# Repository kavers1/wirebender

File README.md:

# Wirebender

This project will build a wire bender

3D designs are shared in STL format. 
The 3D model is available as a Fusion 360 project [Wire bender](https://myhub.autodesk360.com/ue2954c30/g/projects/20200113254731651/data/dXJuOmFkc2sud2lwcHJvZDpmcy5mb2xkZXI6Y28uQzlzSklFZG9SLW1GWHdSQ3duYzF3QQ)

inspiration can be found in 
  - [LiveWire](https://www.thingiverse.com/thing:1786839)
  - [Precise Wire Bending Machine](https://hackaday.io/project/166369-precise-wire-bending-machine)
  - [DIY-wire-bender](https://hackaday.com/2018/10/14/diy-wire-bender-gets-wires-all-bent-into-shape/)

The aim of the project is to combine best of both world and come up with a precise 3D wire bender.

## ESP32-Grbl Controller

This part of the project is based on the project or bdring's [Grbl_ESP32_MPCNC_Controller](https://github.com/bdring/Grbl_ESP32_MPCNC_Controller/) with addition of 2 servo axis, which will be used in our wire bending project.
This ReadMe file is mostly a copy of the original project. As we go we will adapt the content.

This is a CNC controller specially designed to address the needs of the [MPCNC (Mostly Printed CNC) CNC Router](https://www.v1engineering.com/specifications/).
Secondary X and Y axises can be used as servo outputs. This will be usefull for the wirebender project.

### Features

- ESP32 Microcontroller:
  - Very Fast: Dual core 32 bit, 240 MHz
  - Large Flash Memory
  - Wifi:
  - Bluetooth:
- Grbl_ESP32 Firmware:
  - Compatible with most existing Grbl gcode sender software.
  - Web User Interface
  - Multiple Interfaces
    - USB Serial:
    - Web User Interface:
    - Telnet:
    - Bluetooth:
    - SD Card:
- (5) Stepper Motor Drivers: On for each motor in the MPCNC design. Motors are ganging in firmware and have an auto squaring feature executed during homing.
- Limit Switch Connectors: 
- Control Pins:
- Spindle Control:
- Fan Power: 
- Micro SD card: 
- X,Y,Z axis with double motor drivers for X and Y axis drive. These double axis can be disabled and converted to servo axis.

### Credits

To our inspiration [Grbl_ESP32](https://github.com/bdring/Grbl_Esp32)

### Usage Instructions
see original project
[See the wiki](https://github.com/bdring/Grbl_ESP32_MPCNC_Controller/wiki)

### License

Creative Commons Attribution - ShareAlike 4.0 International

There are no commercial restrictions on using this design, but you must attribute the design to Bart Dring or @buildlog. You must also publish any changes or improvements to the design with the same open source license.  

This project is a modification of Bart Drings 

### Version History

- Version 1.0 Original upload ported to Kicad. Added LED support on limits.

### Source Files

- [Firmware](https://github.com/bdring/Grbl_Esp32) to be updated to support servos.
- [Kicad Source](https://github.com/kavers1/wirebender/tree/master/Hardware/ESP32-cnc)
- [Gerber Files](https://github.com/kavers1/wirebender/tree/master/Hardware/ESP32-cnc/gerber)
- [Schematic](https://github.com/kavers1/wirebender/blob/master/Hardware/ESP32-cnc/ESP32-cnc.pdf)
- [imported Kicad Models](https://github.com/kavers1/wirebender/tree/master/Hardware/Kicad_Libs)

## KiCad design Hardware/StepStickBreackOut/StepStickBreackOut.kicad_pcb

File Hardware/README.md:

# Wirebender

## ESP32-Grbl Controller

This project is based on the project or bdring's [Grbl_ESP32_MPCNC_Controller](https://github.com/bdring/Grbl_ESP32_MPCNC_Controller/) with addition of 2 servo axis, which will be used in our wire bending project.
This ReadMe file is mostly a copy of the original project. As we go we will adapt the content.

This is a CNC controller specially designed to address the needs of the [MPCNC (Mostly Printed CNC) CNC Router](https://www.v1engineering.com/specifications/).
Secondary X and Y axises can be used as servo outputs. This will be usefull for the wirebender project.

### Features

- ESP32 Microcontroller:
  - Very Fast: Dual core 32 bit, 240 MHz
  - Large Flash Memory
  - Wifi:
  - Bluetooth:
- Grbl_ESP32 Firmware:
  - Compatible with most existing Grbl gcode sender software.
  - Web User Interface
  - Multiple Interfaces
    - USB Serial:
    - Web User Interface:
    - Telnet:
    - Bluetooth:
    - SD Card:
- (5) Stepper Motor Drivers: On for each motor in the MPCNC design. Motors are ganging in firmware and have an auto squaring feature executed during homing.
- Limit Switch Connectors: 
- Control Pins:
- Spindle Control:
- Fan Power: 
- Micro SD card: 
- X,Y,Z axis with double motor drivers for X and Y axis drive. These double axis can be disabled and converted to servo axis.

### Credits

To our inspiration [Grbl_ESP32](https://github.com/bdring/Grbl_Esp32)

### Usage Instructions
see original project
[See the wiki](https://github.com/bdring/Grbl_ESP32_MPCNC_Controller/wiki)

### License

Creative Commons Attribution - ShareAlike 4.0 International

There are no commercial restrictions on using this design, but you must attribute the design to Bart Dring or @buildlog. You must also publish any changes or improvements to the design with the same open source license.  

This project is a modification of Bart Drings 

### Version History

- Version 1.0 Original upload ported to Kicad. Added LED support on limits.

### Source Files

- [Firmware](https://github.com/bdring/Grbl_Esp32) to be updated to support servos.
- [Kicad Source](https://github.com/kavers1/wirebender/tree/master/Hardware/ESP32-cnc)
- [Gerber Files](https://github.com/kavers1/wirebender/tree/master/Hardware/ESP32-cnc/gerber)
- [Schematic](https://github.com/kavers1/wirebender/blob/master/Hardware/ESP32-cnc/ESP32-cnc.pdf)
- [imported Kicad Models](https://github.com/kavers1/wirebender/tree/master/Hardware/Kicad_Libs)

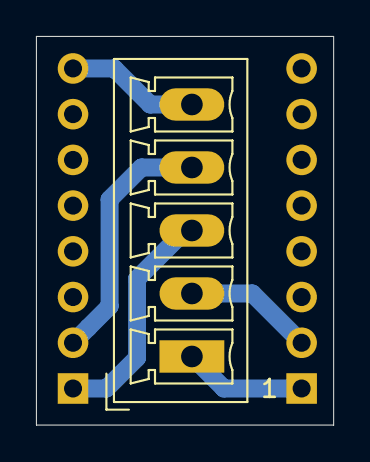
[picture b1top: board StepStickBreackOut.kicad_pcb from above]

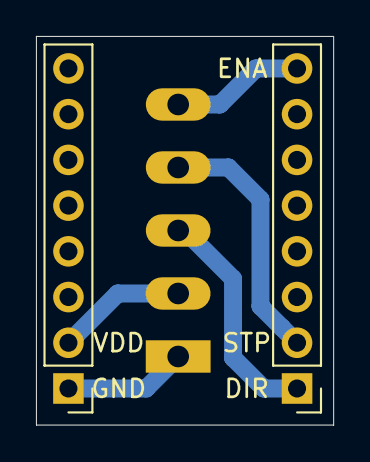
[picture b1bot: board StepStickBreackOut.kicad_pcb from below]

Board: 2 copper layers, 16.5 x 21.6 mm, 3 parts (2 on the bottom side), 5 nets.

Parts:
J1, J3: Conn_01x08; Pin_Header_Straight_1x08_Pitch2.54mm
J2: Screw_Terminal_01x05; PhoenixContact_MCV-G_05x3.50mm_Vertical

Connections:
/DIR: J1.1, J2.3
/ENABLE: J1.8, J2.5
/GND: J2.1, J3.1
/STEP: J1.2, J2.4
/VDD: J2.2, J3.2

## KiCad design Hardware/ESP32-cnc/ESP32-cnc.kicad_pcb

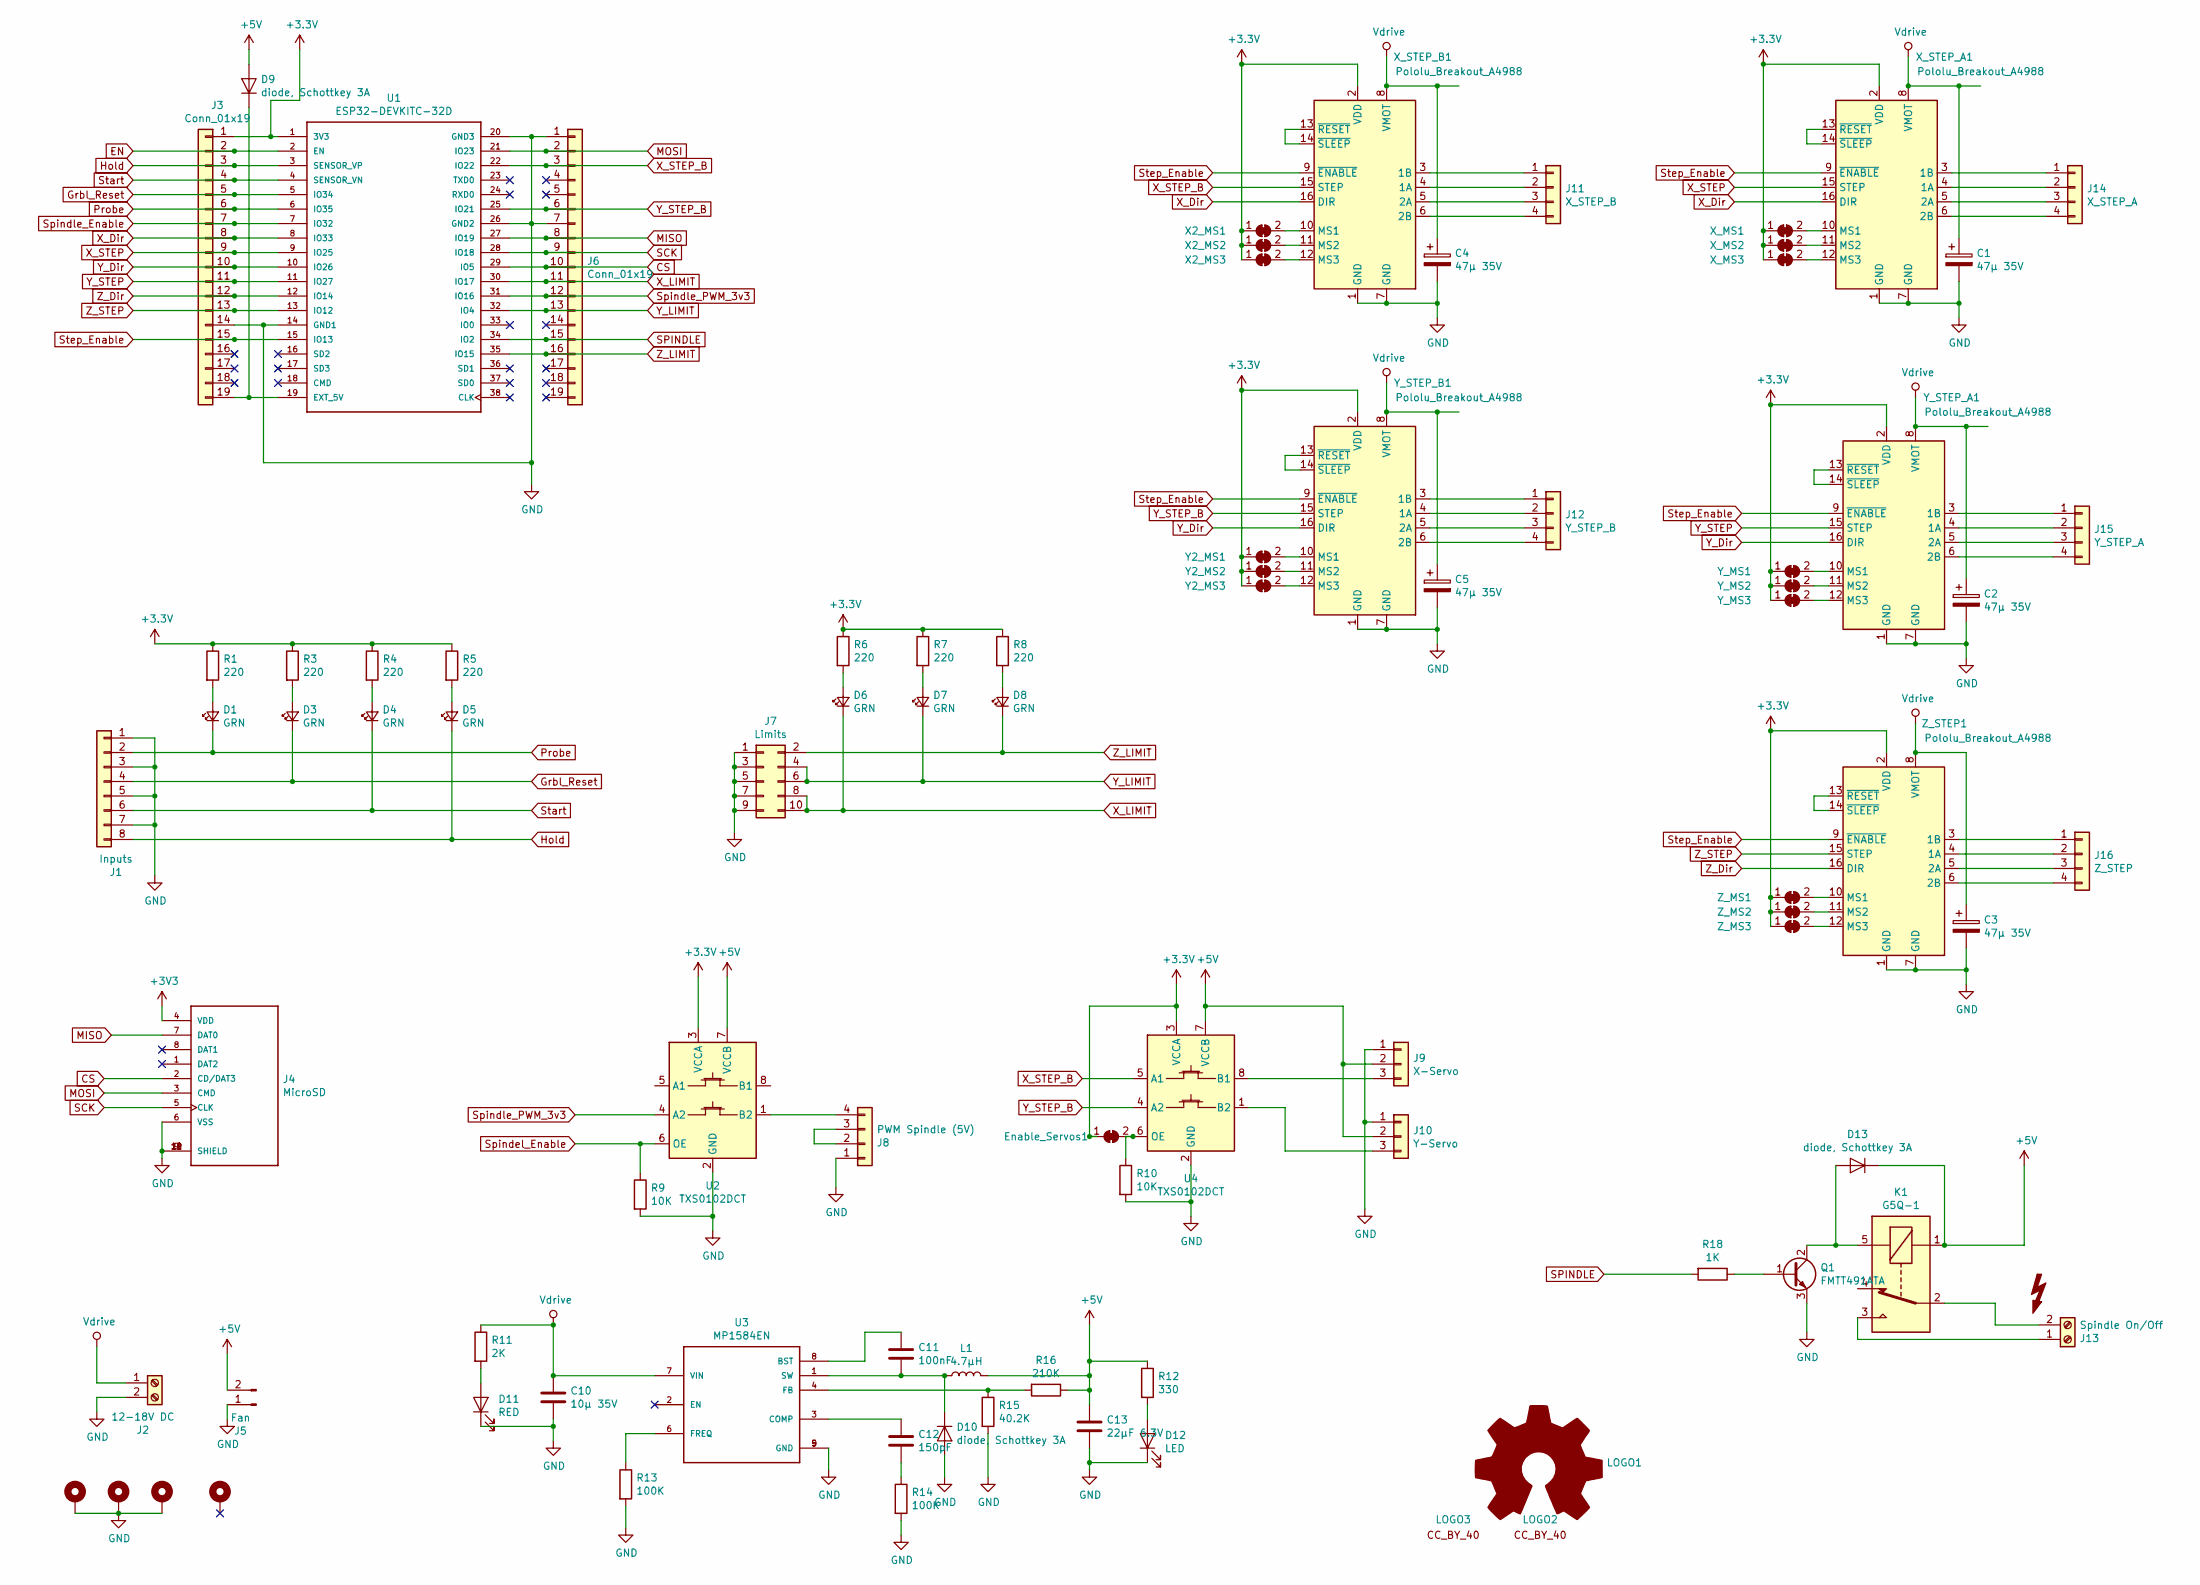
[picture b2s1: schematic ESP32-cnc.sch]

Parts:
C1, C2, C3, C4, C5: 47µ 35V; CP_Elec_6.3x5.3
C10: 10µ 35V; C_1206_HandSoldering
C11: 100nF; C_1206_HandSoldering
C12: 150pF; C_1206_HandSoldering
C13: 22µF 6.3V; C_1206_HandSoldering
D1, D3, D4, D5, D6, D7, D8: GRN; LED_1206_HandSoldering
D9, D10, D13: diode, Schottkey 3A; D_SMA_Handsoldering
D11: RED; LED_1206_HandSoldering
D12: LED; LED_1206_HandSoldering
Enable_Servos1: Enable_Servos; SolderJumper-2_P1.3mm_Bridged_RoundedPad1.0x1.5mm
H1, H2, H3, H4: MountingHole_Pad; MountingHole_4.3mm_M4_DIN965_Pad
J1: Inputs; Pin_Header_Straight_1x08_Pitch2.54mm
J2: 12-18V DC; TerminalBlock_Altech_AK300-2_P5.00mm
J3, J6: Conn_01x19; Pin_Header_Straight_1x19_Pitch2.54mm
J4: MicroSD; GCT_MEM2067-02-180-00-A_REVB
J5: Fan; Pin_Header_Straight_1x02_Pitch2.54mm
J7: Limits; Pin_Header_Straight_2x05_Pitch2.54mm
J8: PWM Spindle (5V); Pin_Header_Straight_1x04_Pitch2.54mm
J9: X-Servo; Pin_Header_Straight_1x03_Pitch2.54mm
J10: Y-Servo; Pin_Header_Straight_1x03_Pitch2.54mm
J11: X_STEP_B; Pin_Header_Straight_1x04_Pitch2.54mm
J12: Y_STEP_B; Pin_Header_Straight_1x04_Pitch2.54mm
J13: Spindle On/Off; TerminalBlock_Altech_AK300-2_P5.00mm
J14: X_STEP_A; Pin_Header_Straight_1x04_Pitch2.54mm
J15: Y_STEP_A; Pin_Header_Straight_1x04_Pitch2.54mm
J16: Z_STEP; Pin_Header_Straight_1x04_Pitch2.54mm
K1: G5Q-1; Relay_SPDT_OMRON-G5Q
L1: 4.7µH; Inductor_1212
LOGO1: Logo_Open_Hardware_Large; OSHW-Symbol_22.3x20mm_SilkScreen
LOGO2: SYM_CC_BY; Symbol_CreativeCommonsPublicDomain_SilkScreenTop_Small
LOGO3: SYM_CC_BY; Symbol_CC-Attribution_CopperTop_Small
Q1: FMTT491ATA; SOT-23
R1, R3, R4, R5, R6, R7, R8: 220; R_1206_HandSoldering
R9, R10: 10K; R_1206_HandSoldering
R11: 2K; R_1206_HandSoldering
R12: 330; R_1206_HandSoldering
R13, R14: 100K; R_1206_HandSoldering
R15: 40.2K; R_1206_HandSoldering
R16: 210K; R_1206_HandSoldering
R18: 1K; R_1206_HandSoldering
SYM1: SYM_Flash_Small; Symbol_HighVoltage_Type2_CopperTop_VerySmall
U1: ESP32-DEVKITC-32D; MODULE_ESP32-DEVKITC-32D
U2, U4: TXS0102DCT; SOP65P400X130-8N
U3: MP1584EN; SOIC127P600X170-9N
X2_MS1: X2_MS1; SolderJumper-2_P1.3mm_Bridged_RoundedPad1.0x1.5mm
X2_MS2: X2_MS2; SolderJumper-2_P1.3mm_Bridged_RoundedPad1.0x1.5mm
X2_MS3: X2_MS3; SolderJumper-2_P1.3mm_Bridged_RoundedPad1.0x1.5mm
X_MS1: X_MS1; SolderJumper-2_P1.3mm_Bridged_RoundedPad1.0x1.5mm
X_MS2: X_MS2; SolderJumper-2_P1.3mm_Bridged_RoundedPad1.0x1.5mm
X_MS3: X_MS3; SolderJumper-2_P1.3mm_Bridged_RoundedPad1.0x1.5mm
X_STEP_A1: Pololu_Breakout_A4988; MODULE_A4988_STEPPER_MOTOR_DRIVER_CARRIER
X_STEP_B1: Pololu_Breakout_A4988; MODULE_A4988_STEPPER_MOTOR_DRIVER_CARRIER
Y2_MS1: Y2_MS1; SolderJumper-2_P1.3mm_Bridged_RoundedPad1.0x1.5mm
Y2_MS2: Y2_MS2; SolderJumper-2_P1.3mm_Bridged_RoundedPad1.0x1.5mm
Y2_MS3: Y2_MS3; SolderJumper-2_P1.3mm_Bridged_RoundedPad1.0x1.5mm
Y_MS1: Y_MS1; SolderJumper-2_P1.3mm_Bridged_RoundedPad1.0x1.5mm
Y_MS2: Y_MS2; SolderJumper-2_P1.3mm_Bridged_RoundedPad1.0x1.5mm
Y_MS3: Y_MS3; SolderJumper-2_P1.3mm_Bridged_RoundedPad1.0x1.5mm
Y_STEP_A1: Pololu_Breakout_A4988; MODULE_A4988_STEPPER_MOTOR_DRIVER_CARRIER
Y_STEP_B1: Pololu_Breakout_A4988; MODULE_A4988_STEPPER_MOTOR_DRIVER_CARRIER
Z_MS1: Z_MS1; SolderJumper-2_P1.3mm_Bridged_RoundedPad1.0x1.5mm
Z_MS2: Z_MS2; SolderJumper-2_P1.3mm_Bridged_RoundedPad1.0x1.5mm
Z_MS3: Z_MS3; SolderJumper-2_P1.3mm_Bridged_RoundedPad1.0x1.5mm
Z_STEP1: Pololu_Breakout_A4988; MODULE_A4988_STEPPER_MOTOR_DRIVER_CARRIER

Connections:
+5V: C13.1, D9.2 (A), D13.1 (K), J5.2, J9.2, J10.2, K1.1, L1.2, R12.1, R16.1, U2.7 (VCCB), U4.7 (VCCB)
CS: J4.2 (CD/DAT3), J6.10, U1.29 (IO5)
EN: J3.2, U1.2 (EN)
GND: C1.2, C2.2, C3.2, C4.2, C5.2, C10.2, C13.2, D10.2 (A), D11.1 (K), D12.1 (K), H1.1, H2.1, H3.1, J1.1, J1.3, J1.5, J1.7, J2.2, J3.14, J4.6 (VSS), J4.9 (SHIELD), J4.10 (SHIELD), J4.11 (SHIELD), J4.12 (SHIELD), J5.1, J6.1, J6.7, J7.1, J7.3, J7.5, J7.7, J7.9, J8.1, J9.1, J10.1, Q1.3 (E), R9.2, R10.2, R13.2, R14.2, R15.2, U1.14 (GND1), U1.20 (GND3), U1.26 (GND2), U2.2 (GND), U3.5 (GND), U3.9 (GND), U4.2 (GND), X_STEP_A1.1 (GND), X_STEP_A1.7 (GND), X_STEP_B1.1 (GND), X_STEP_B1.7 (GND), Y_STEP_A1.1 (GND), Y_STEP_A1.7 (GND), Y_STEP_B1.1 (GND), Y_STEP_B1.7 (GND), Z_STEP1.1 (GND), Z_STEP1.7 (GND)
Grbl_Reset: D3.1 (K), J1.4, J3.5, U1.5 (IO34)
Hold: D5.1 (K), J1.8, J3.3, U1.3 (SENSOR_VP)
MISO: J4.7 (DAT0), J6.8, U1.27 (IO19)
MOSI: J4.3 (CMD), J6.2, U1.21 (IO23)
unnamed: C11.1, U3.8 (BST)
unnamed: C11.2, D10.1 (K), L1.1, U3.1 (SW)
unnamed: C12.1, U3.3 (COMP)
unnamed: C12.2, R14.1
unnamed: D1.2 (A), R1.2
unnamed: D3.2 (A), R3.2
unnamed: D4.2 (A), R4.2
unnamed: D5.2 (A), R5.2
unnamed: D6.2 (A), R6.2
unnamed: D7.2 (A), R7.2
unnamed: D8.2 (A), R8.2
unnamed: D9.1 (K), J3.19, U1.19 (EXT_5V)
unnamed: D11.2 (A), R11.2
unnamed: D12.2 (A), R12.2
unnamed: D13.2 (A), K1.5, Q1.2 (C)
unnamed: Enable_Servos1.2 (B), R10.1, U4.6 (OE)
unnamed: J8.2, J8.3
unnamed: J8.4, U2.1 (B2)
unnamed: J9.3, U4.8 (B1)
unnamed: J10.3, U4.1 (B2)
unnamed: J11.1, X_STEP_B1.3 (1B)
unnamed: J11.2, X_STEP_B1.4 (1A)
unnamed: J11.3, X_STEP_B1.5 (2A)
unnamed: J11.4, X_STEP_B1.6 (2B)
unnamed: J12.1, Y_STEP_B1.3 (1B)
unnamed: J12.2, Y_STEP_B1.4 (1A)
unnamed: J12.3, Y_STEP_B1.5 (2A)
unnamed: J12.4, Y_STEP_B1.6 (2B)
unnamed: J13.1, K1.3
unnamed: J13.2, K1.2
unnamed: J14.1, X_STEP_A1.3 (1B)
unnamed: J14.2, X_STEP_A1.4 (1A)
unnamed: J14.3, X_STEP_A1.5 (2A)
unnamed: J14.4, X_STEP_A1.6 (2B)
unnamed: J15.1, Y_STEP_A1.3 (1B)
unnamed: J15.2, Y_STEP_A1.4 (1A)
unnamed: J15.3, Y_STEP_A1.5 (2A)
unnamed: J15.4, Y_STEP_A1.6 (2B)
unnamed: J16.1, Z_STEP1.3 (1B)
unnamed: J16.2, Z_STEP1.4 (1A)
unnamed: J16.3, Z_STEP1.5 (2A)
unnamed: J16.4, Z_STEP1.6 (2B)
unnamed: Q1.1 (B), R18.1
unnamed: R13.1, U3.6 (FREQ)
unnamed: R15.1, R16.2, U3.4 (FB)
unnamed: X2_MS1.2 (B), X_STEP_B1.10 (MS1)
unnamed: X2_MS2.2 (B), X_STEP_B1.11 (MS2)
unnamed: X2_MS3.2 (B), X_STEP_B1.12 (MS3)
unnamed: X_MS1.2 (B), X_STEP_A1.10 (MS1)
unnamed: X_MS2.2 (B), X_STEP_A1.11 (MS2)
unnamed: X_MS3.2 (B), X_STEP_A1.12 (MS3)
unnamed: X_STEP_A1.13 (~RESET), X_STEP_A1.14 (~SLEEP)
unnamed: X_STEP_B1.13 (~RESET), X_STEP_B1.14 (~SLEEP)
unnamed: Y2_MS1.2 (B), Y_STEP_B1.10 (MS1)
unnamed: Y2_MS2.2 (B), Y_STEP_B1.11 (MS2)
unnamed: Y2_MS3.2 (B), Y_STEP_B1.12 (MS3)
unnamed: Y_MS1.2 (B), Y_STEP_A1.10 (MS1)
unnamed: Y_MS2.2 (B), Y_STEP_A1.11 (MS2)
unnamed: Y_MS3.2 (B), Y_STEP_A1.12 (MS3)
unnamed: Y_STEP_A1.13 (~RESET), Y_STEP_A1.14 (~SLEEP)
unnamed: Y_STEP_B1.13 (~RESET), Y_STEP_B1.14 (~SLEEP)
unnamed: Z_MS1.2 (B), Z_STEP1.10 (MS1)
unnamed: Z_MS2.2 (B), Z_STEP1.11 (MS2)
unnamed: Z_MS3.2 (B), Z_STEP1.12 (MS3)
unnamed: Z_STEP1.13 (~RESET), Z_STEP1.14 (~SLEEP)
Probe: D1.1 (K), J1.2, J3.6, U1.6 (IO35)
SCK: J4.5 (CLK), J6.9, U1.28 (IO18)
SPINDLE: J6.15, R18.2, U1.34 (IO2)
Spindel_Enable: R9.1, U2.6 (OE)
Spindle_Enable: J3.7, U1.7 (IO32)
Spindle_PWM_3v3: J6.12, U1.31 (IO16), U2.4 (A2)
Start: D4.1 (K), J1.6, J3.4, U1.4 (SENSOR_VN)
Step_Enable: J3.15, U1.15 (IO13), X_STEP_A1.9 (~ENABLE), X_STEP_B1.9 (~ENABLE), Y_STEP_A1.9 (~ENABLE), Y_STEP_B1.9 (~ENABLE), Z_STEP1.9 (~ENABLE)
Vdrive: C1.1, C2.1, C3.1, C4.1, C5.1, C10.1, J2.1, R11.1, U3.7 (VIN), X_STEP_A1.8 (VMOT), X_STEP_B1.8 (VMOT), Y_STEP_A1.8 (VMOT), Y_STEP_B1.8 (VMOT), Z_STEP1.8 (VMOT)
X_Dir: J3.8, U1.8 (IO33), X_STEP_A1.16 (DIR), X_STEP_B1.16 (DIR)
X_LIMIT: D6.1 (K), J6.11, J7.8, J7.10, U1.30 (IO17)
X_STEP: J3.9, U1.9 (IO25), X_STEP_A1.15 (STEP)
X_STEP_B: J6.3, U1.22 (IO22), U4.5 (A1), X_STEP_B1.15 (STEP)
Y_Dir: J3.10, U1.10 (IO26), Y_STEP_A1.16 (DIR), Y_STEP_B1.16 (DIR)
Y_LIMIT: D7.1 (K), J6.13, J7.4, J7.6, U1.32 (IO4)
Y_STEP: J3.11, U1.11 (IO27), Y_STEP_A1.15 (STEP)
Y_STEP_B: J6.6, U1.25 (IO21), U4.4 (A2), Y_STEP_B1.15 (STEP)
Z_Dir: J3.12, U1.12 (IO14), Z_STEP1.16 (DIR)
Z_LIMIT: D8.1 (K), J6.16, J7.2, U1.35 (IO15)
Z_STEP: J3.13, U1.13 (IO12), Z_STEP1.15 (STEP)

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
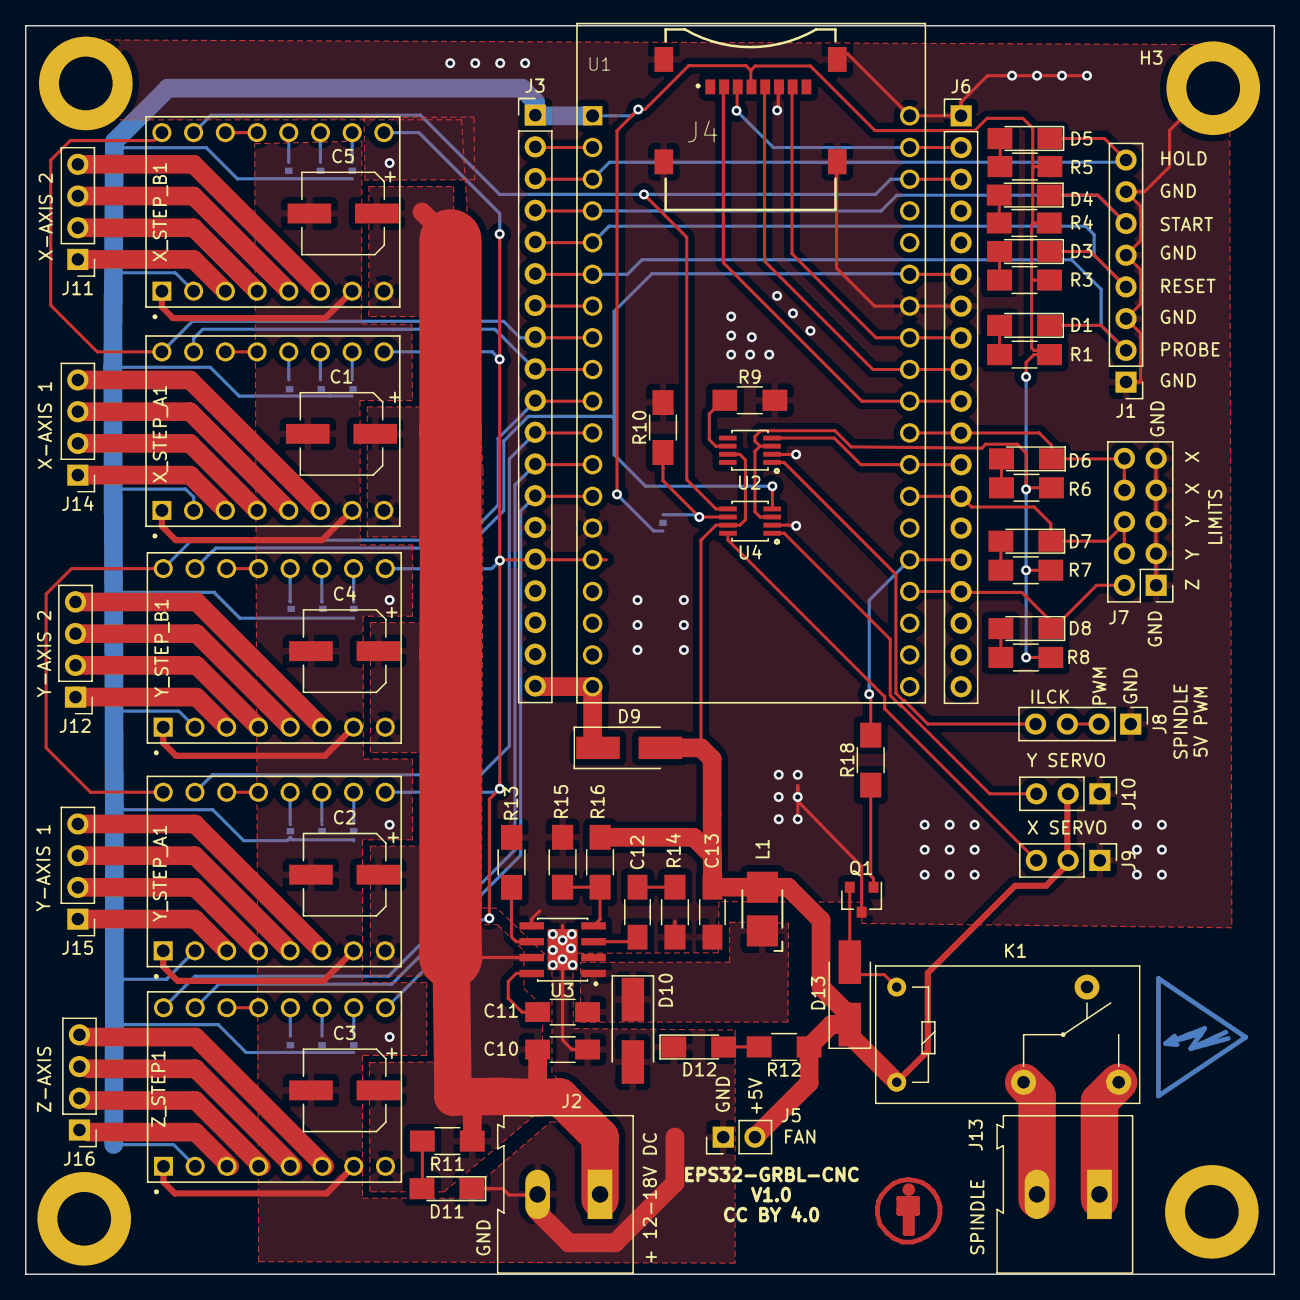
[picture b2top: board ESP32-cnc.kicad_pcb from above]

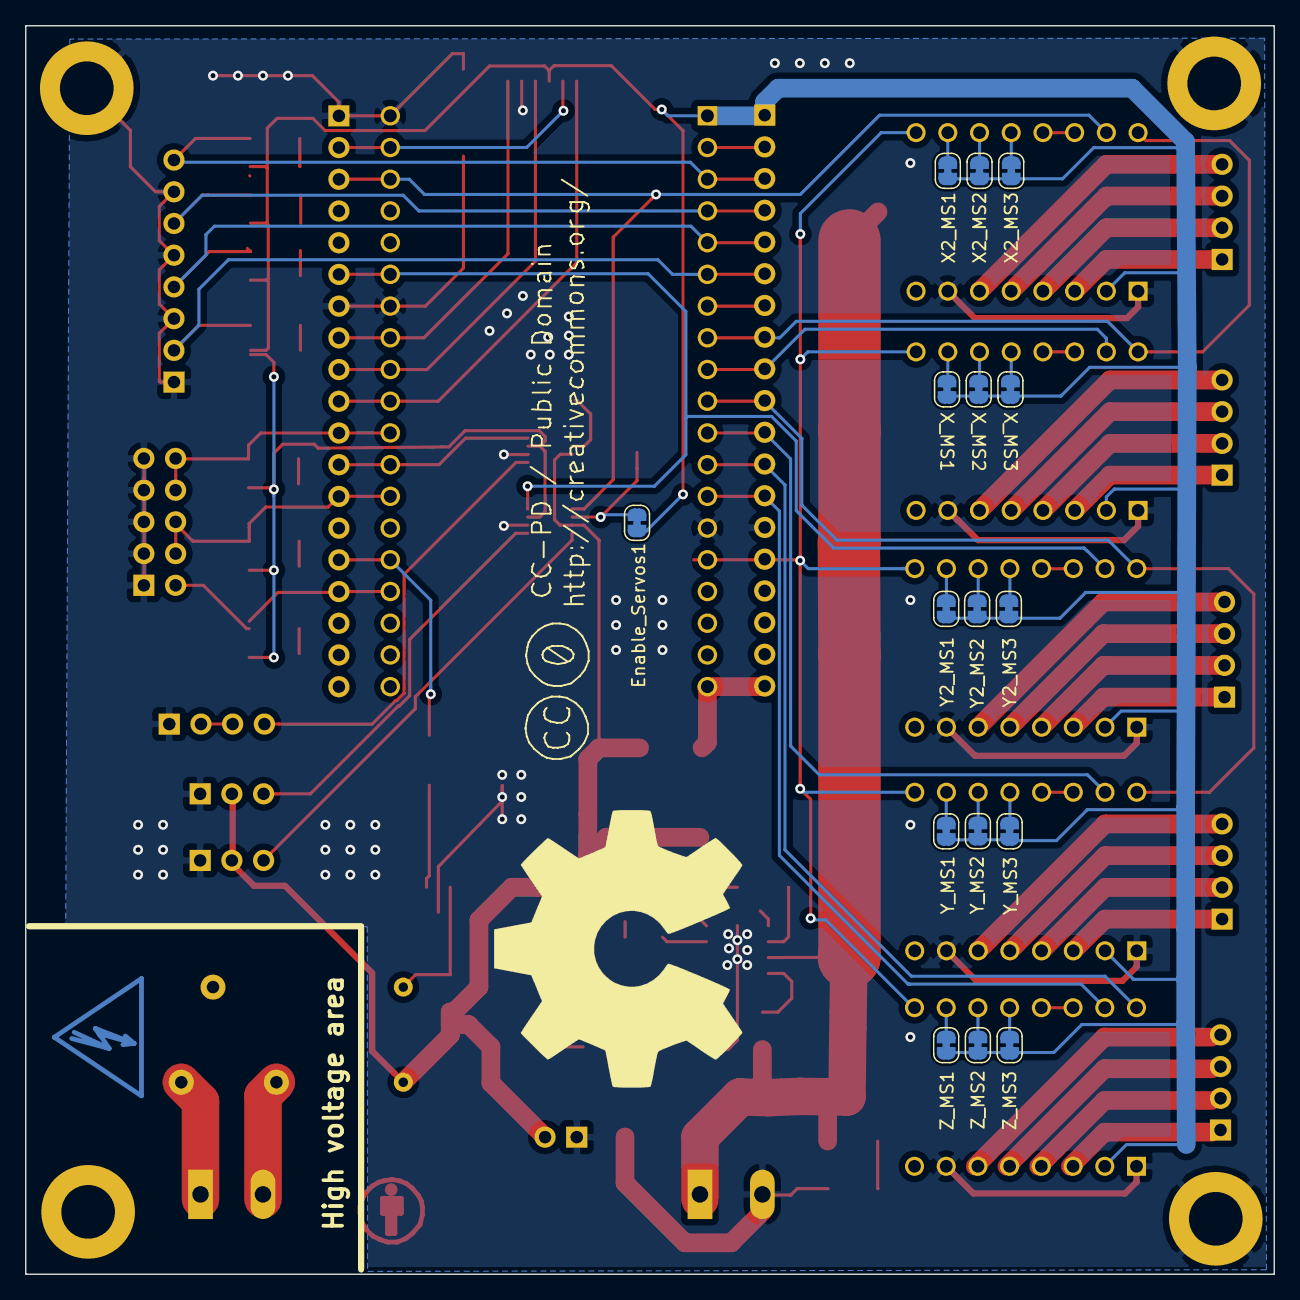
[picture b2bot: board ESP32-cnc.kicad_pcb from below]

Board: 2 copper layers, 100.0 x 100.0 mm, 89 parts (19 on the bottom side), 94 nets.

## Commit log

2020-01-26 Rev 1
2020-01-26 minor updates
2020-01-26 link corrections
2020-01-26 reshuffle
2020-01-26 footprint adaption
2020-01-26 fixed broken links
2020-01-26 update axis
2020-01-27 updated info
2020-01-27 typo
2020-01-27 a space to much
2020-02-01 added break out for stepper driver

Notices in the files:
Hardware/ESP32-cnc/ESP32-cnc.kicad_pcb:
CC BY 4.0
